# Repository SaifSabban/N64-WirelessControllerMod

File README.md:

# N64 -Wireless Controller Mod
A modification to your current N64 controller to make it wireless. Based on the Work by micro on the [Universal Wireless Retro Controller](https://nfggames.com/forum2/index.php?topic=5180.0) Click the photo to see a video of the controller in action.

<p align="center">

<p>

[!Youtube Tutorial Link (.../Extra/Images/Face.png)](http://www.youtube.com/shorts/WrgqsBNa95k)

<p align="center">
<iframe width="560 hight="315" src="http://www.youtube.com/shorts/WrgqsBNa95k" title="Youtube Tutorial Link" frameboarder="0"allow="accelerometer; autoplay; clipboard-write; encrypted-media; gyroscope; picture-in-picture" allowfullscreen></iframe>
</p>

href="http://www.youtube.com/shorts/WrgqsBNa95k" target="_blank"></a>
<p>

### Notes
This project could use a lot of work, mainly:
1. We could integrate the NRF24L01+ into the PCB boards.
2. Add the components of the Micro-LiPo into the main transmitter PCB Board.
3. Translate the assembly code into Arduino code to allow the use of smaller micro controllers and possibly 2-way communication.

If you press the A button while powering the N64 controller with the mod, you will set the channel to A, while if you press B, you will set it to Channel B.

Know that if you decide to undertake this project, you are the one liable for any damages or risks that might occur.

## Getting Started
### Prerequisites
All the Components that are needed can be found in the bellow list:
<p align="center"><p>

Optionally you could use JST connectors, instead of soldering wires directly to the PCB. I used the PH series.<br/>
you need to have an [ISP Arduino Programmer](https://docs.arduino.cc/built-in-examples/arduino-isp/ArduinoISP), or use any ISP programmer such as the [USBasp-Programmer](https://hobbycomponents.com/usb-interface/841-usbasp-avr-programmer-adaptor).<br/>
Install and set up [avrdudess](https://avrdudess.software.informer.com/2.4/) There are tons of write-ups on how to do this.<br/>
Print the Receiver's [3D box and Lid](https://github.com/saifsabban/N64-WirelessControllerMod/tree/master/3D-PrintableCase), and use two 2.5M screws to hold it down.<br/>
Print the PCBs for the [Reciever with a SMD microcontroller](https://github.com/saifsabban/N64-WirelessControllerMod/blob/master/N64_Receiver/N64_Receiver_PCB/N64_RX_GerberV2.1.zip) or [Receiver with a DIP microcontroller](https://github.com/saifsabban/N64-WirelessControllerMod/blob/master/N64_Receiver/N64_Receiver_PCB/N64_RX_GerberV2.0.zip) & the [Transmitter](https://github.com/saifsabban/N64-WirelessControllerMod/blob/master/N64_Transmitter/N64_Transmitter_PCB/N64_Tx_V4.0_Gerber.zip)

## Making the Receiver
1. Populate the Receiver PCB with the appropriate parts (The essential resistors & capacitor can be either SMD or Through-Hole):<br/><p align="center"><p>
2. Connect the ISP pins for your desired programmer to the Receiver Board. Hopefully this reference image and the PCB silkscreen will be of some help.<br/><p align="center"><p>
3. Program the Board using AVRdudess with the same parameters shown, MAKE SURE THAT THE HIGH BYTE IS 0xDF & LOW BYTE IS 0xEE. If you don't then you might never be able to use that microcontroller again unless you change the crystal<br/><p align="center"><p>
4. Solder some wire to the switch and solder the other side to the PCB board's SW connector (It doesn't matter which pole of the switch connects to which pad).
5. Cut the N64 plug from the controller, making sure you have some length to route & solder to, I usually keep amount 20cm of cable and cut as necessary.
6. Check the fit of the plug to the printed box, some 3D printers make the opening too large or too small.
7. Glue the Connector to the BOX.
8. Solder the Red wire to the + pad on the connector labelled N64, the black wire to the pad labelled - and the white wire to the pad in the middle of both + & -.
9. Attach (or solder) the NRF24L01+ board onto the Receiver PCB.
10. Place and glue all the parts inside the 3D printed box (As shown) and screw on the Lid<br/><p align="center"><p>

## Making the Transmitters
1. Populate the Transmitter PCB with the appropriate parts:<br/><p align="center"><p>
2. Connect the ISP pins for your desired programmer to the Transmitter Board. Hopefully this reference image will be of some help (the pins are in the same location as the connector on the Transmitter PCB, the Ground pin is the one that is highlighted)<br/><p align="center"><p>
3. Program the Board using AVRdudess with the same parameters shown, MAKE SURE THAT THE HIGH BYTE IS 0xDF & LOW BYTE IS 0xDF. If you don't then you might never be able to use that microcontroller again unless you change the crystal<br/><p align="center"><p>
4. Disassemble the N64 Controller.
5. Desolder the original blue connector that connects to the cable. (I would strongly advise soldering a JST 4 pin PH female connector as shown in the photo below)<br/><p align="center"><p>
6. Check the Size of your switch as around 4.8mm, and proceed to drill a 5mm hole at the button half of the controller (See images), solder some wires to them and screw them onto the controller<br/><p align="center"><p><br/><p align="center"><p>
7. Solder some wires to the 5mm LED and hotglue it into the hole that the old controller wire used to come out of. (Keep a note which wire is positive and which is negative) <br/><p align="center"><p>
8. route the wires switch and LED wires to the "Right Hand" area of the controller.<br/><p align="center"><p>
9. Remove the 2 lower "Crosses" that brace the buttons, from the bottom half of the controller.<br/><p align="center"><p>
10. solder wires to the "Bat" pin and the "GND" pin on the Adafruit Micro lipo.
11. Place the Micro lipo at the Right-hand side of the controller, and cut a bit off the corresponding top and bottom half edges to allow the USB charger through.<br/><p align="center"><p><br/><p align="center"><p>
12. Desolder the Pins on the NRF24L01+ and solder wires to each pin, remembering which wire corresponds to which pin.<br/><p align="center"><p>
13. leave some length and solder the other side of the wires from step 11 to the Custom board.<br/><p align="center"><p>
14. Solder the LED and Switch wires to the Main PCB, making sure the polarity of the LED wires are correct (- pin is Ground, + pin is 3.3V).
15. Solder the wires from the Micro lipo, to the Custom board's Bat pins, making sure that the Bat pin solders to the pin marked with a +.
16. Solder the wires From the N64 controller board to the custom board, Pin order is VCC (Denoted by the + sign on top), signal wire, and ground. <br/><p align="center"><p>
17. Attach a battery to the micro lipo and test the mod. Remember if you press the A button while powering the N64 controller with the mod, you will set the channel to A, while if you press B, you will set it to Channel B.
18. If all works button up your device. I recommend routing the battery to the Left hand side of the controller, the custom board to the Right, and feeding the NRF24L01+ into the nook of the expantion slot.<br/><p align="center"><p>

## Warnings!!
Make sure the polarity of the receiver pins is correct or you risk blowing the N64's power module, or worse, frying the N64 completely. In you connect the Batter pins or the N64 pins to the wrong wires you risk frying you N64 controller. I've tried this mod on reproduction N64 controllers, but it seems they allow some electrical noise that messes us the communication pathways and making it seem like you've pressed buttons you didn't actually press. If you mess with the power pins on the NRF24L01+ you risk breaking either your n64 or the controller, depending on which one was wrongfully connected. However, messing up the data pins of the NRF24L01+ breaks nothing. If the battery is too low, it will keep the LED light on, but might not send any control signals to the receiver.

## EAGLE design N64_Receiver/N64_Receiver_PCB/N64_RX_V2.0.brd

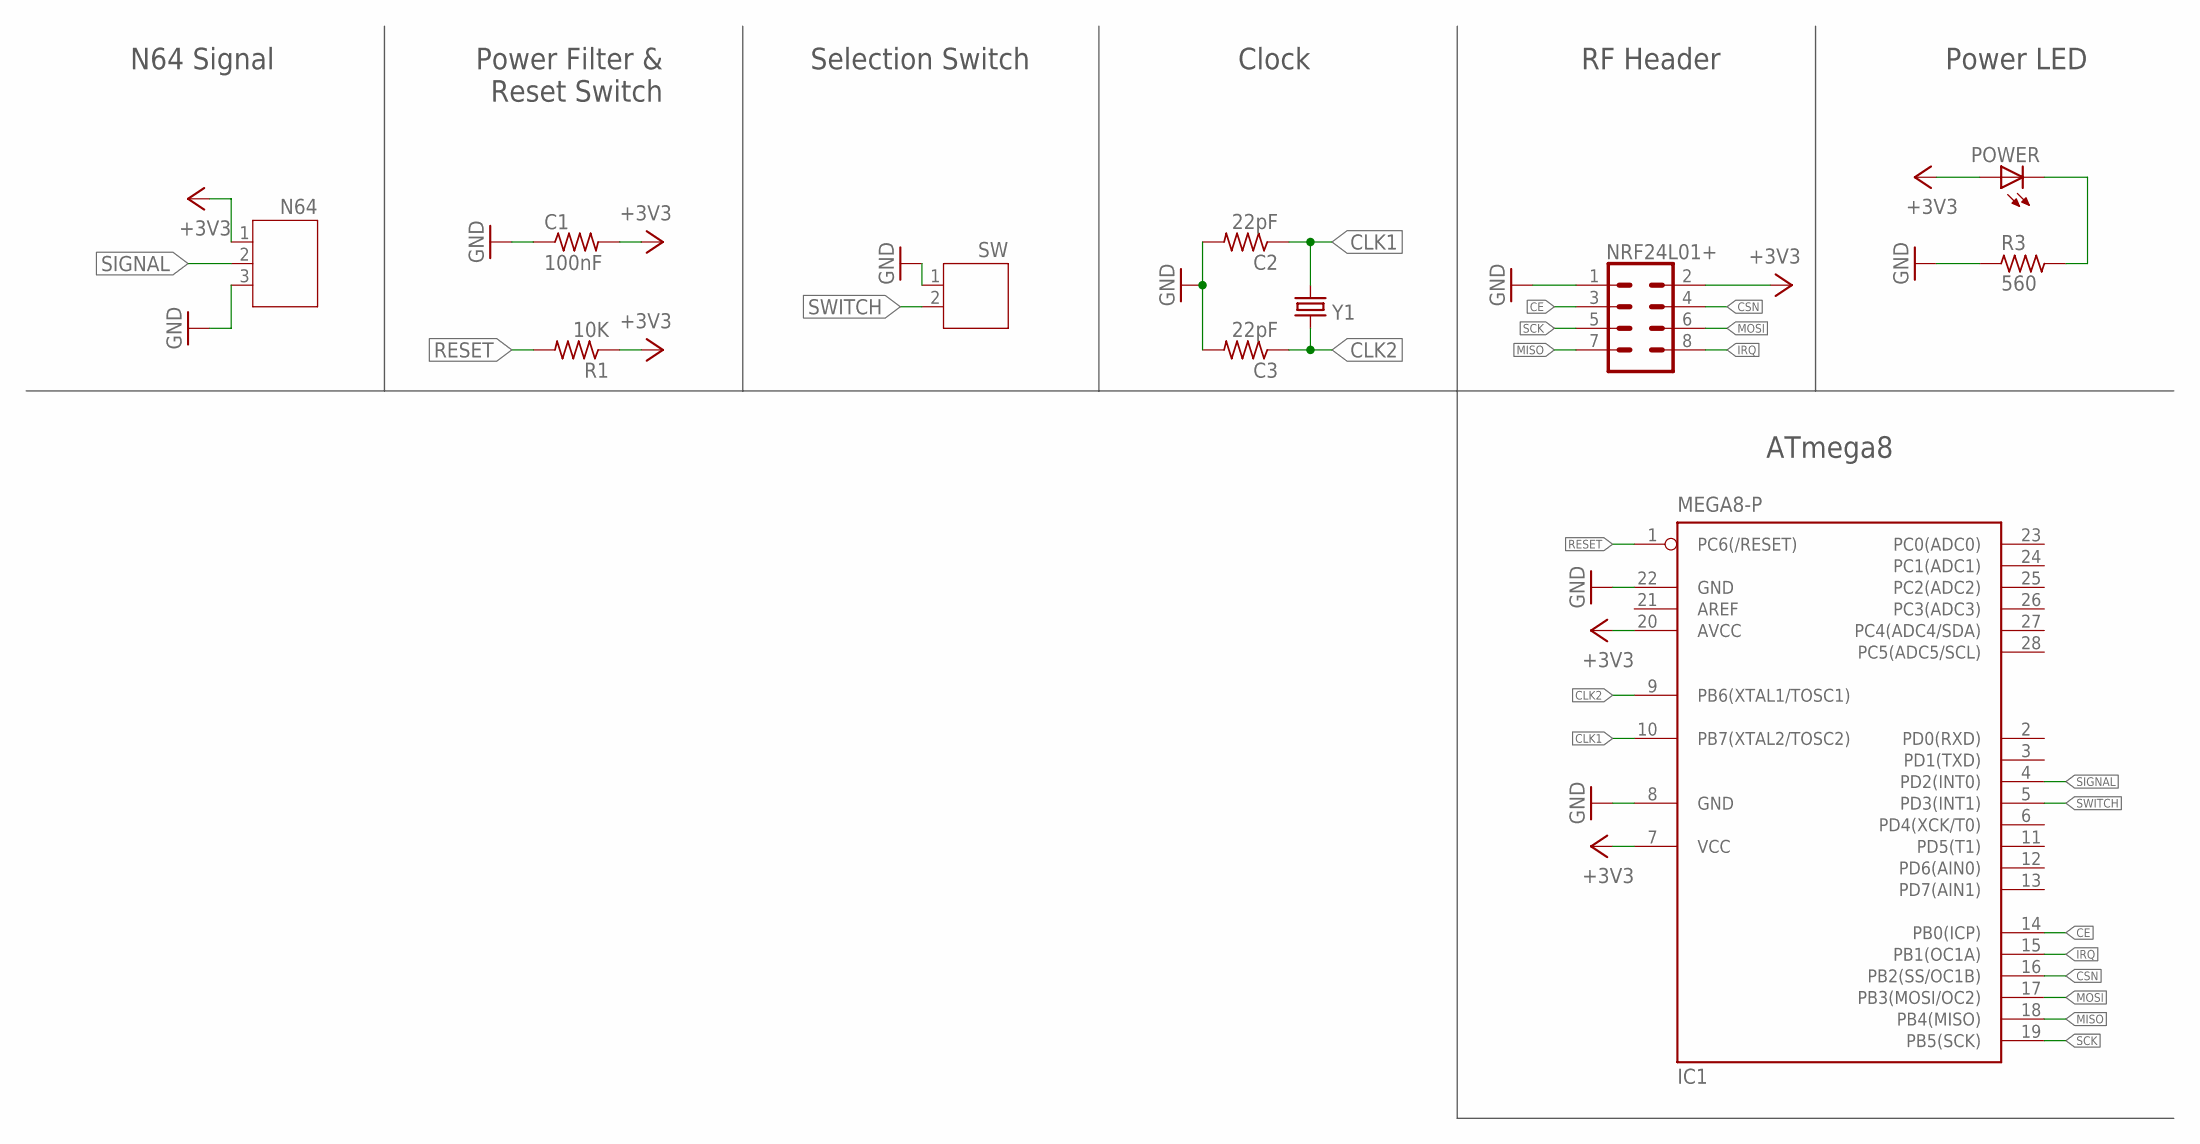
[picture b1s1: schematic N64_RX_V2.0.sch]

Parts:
C1: 100nF; 0805-THM
C2, C3: 22pF; 0805-THM
IC1: MEGA8-P; DIL28-3
N64: JST-PH3TH; JST-PH3
NRF24L01+: CONN_04X2; 2X4
POWER: LEDCHIPLED_0805; CHIPLED_0805
R1: 10K; 0805-THM
R3: 560; R0805
SW: JST-PH2TH; JST-PH2
Y1: CRYSTALHC49S; HC49/S

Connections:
+3V3: C1.2, IC1.7 (VCC), IC1.20 (AVCC), N64.1, NRF24L01+.2, POWER.A, R1.1
CE: IC1.14 (PB0(ICP)), NRF24L01+.3
CLK1: C2.1, IC1.10 (PB7(XTAL2/TOSC2)), Y1.2
CLK2: C3.1, IC1.9 (PB6(XTAL1/TOSC1)), Y1.1
CSN: IC1.16 (PB2(SS/OC1B)), NRF24L01+.4
GND: C1.1, C2.2, C3.2, IC1.8 (GND), IC1.22 (GND), N64.3, NRF24L01+.1, R3.1, SW.1
IRQ: IC1.15 (PB1(OC1A)), NRF24L01+.8
MISO: IC1.18 (PB4(MISO)), NRF24L01+.7
MOSI: IC1.17 (PB3(MOSI/OC2)), NRF24L01+.6
unnamed: POWER.C, R3.2
RESET: IC1.1 (PC6(/RESET)), R1.2
SCK: IC1.19 (PB5(SCK)), NRF24L01+.5
SIGNAL: IC1.4 (PD2(INT0)), N64.2
SWITCH: IC1.5 (PD3(INT1)), SW.2

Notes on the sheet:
N64 Signal
Power Filter & Reset Switch
Selection Switch
Clock
RF Header
ATmega8
Power LED

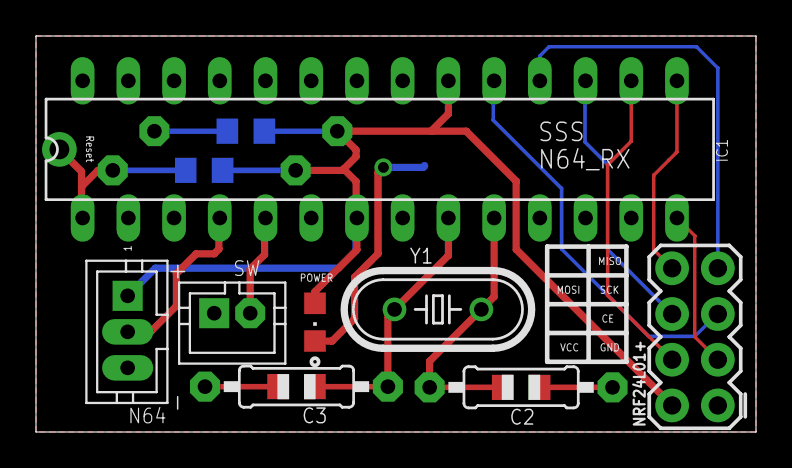
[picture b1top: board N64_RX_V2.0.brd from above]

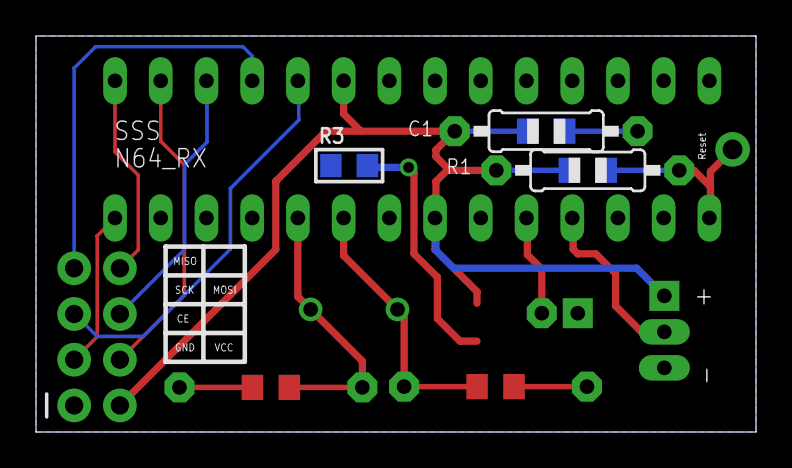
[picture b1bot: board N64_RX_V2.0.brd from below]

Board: 2 copper layers, 40.0 x 22.0 mm, 11 parts (3 on the bottom side), 14 nets.

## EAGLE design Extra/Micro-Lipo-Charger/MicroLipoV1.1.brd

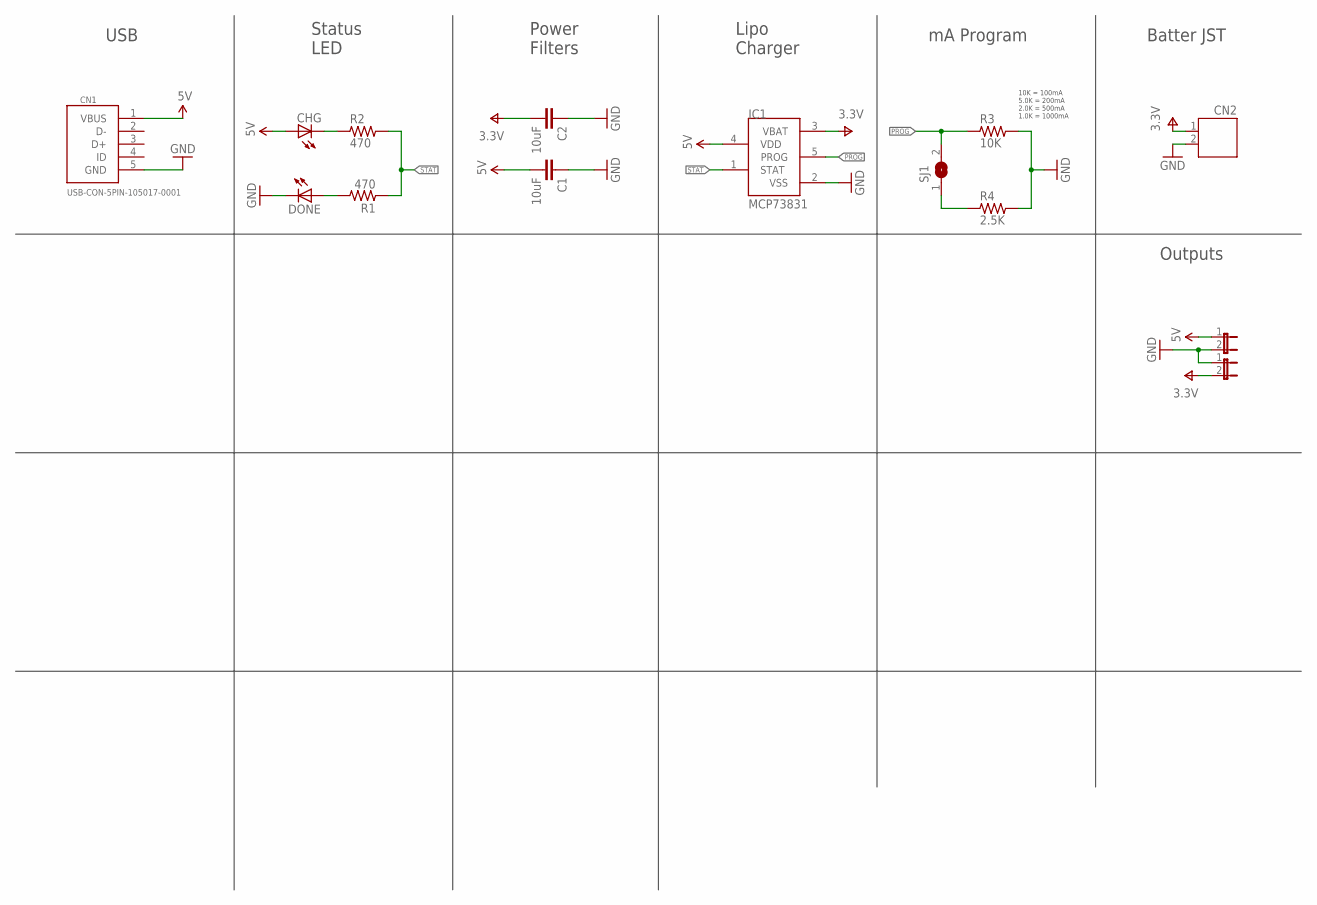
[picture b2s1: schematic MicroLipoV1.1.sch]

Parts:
C1, C2: 10uF; C0805K
CHG: LEDCHIPLED_0805; CHIPLED_0805
CN1: USB-CON-5PIN-105017-0001; USB-MICRO-MOLEX-105017-0001
CN2: JST-PH2; JST-PH2-S2B
DONE: LEDCHIPLED_0805; CHIPLED_0805
IC1: MCP73831; SOT23-5L
JP2, JP3: JUMPER-2PTH; 1X02
R1, R2: 470; R0805
R3: 10K; R0805
R4: 2.5K; R0805
SJ1: SJ

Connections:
5V: C1.2, CHG.A, CN1.1 (VBUS), IC1.4 (VDD), JP2.1
GND: C1.1, C2.1, CN1.5 (GND), CN2.2, DONE.C, IC1.2 (VSS), JP2.2, JP3.1, R3.2, R4.2
unnamed: CHG.C, R2.1
unnamed: DONE.A, R1.2
unnamed: R4.1, SJ1.1
PROG: IC1.5 (PROG), R3.1, SJ1.2
STAT: IC1.1 (STAT), R1.1, R2.2
V+: C2.2, CN2.1, IC1.3 (VBAT), JP3.2

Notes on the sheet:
USB
Status LED
Power Filters
Lipo Charger
mA Program
Batter JST
Outputs
10K = 100mA 5.0K = 200mA 2.0K = 500mA 1.0K = 1000mA

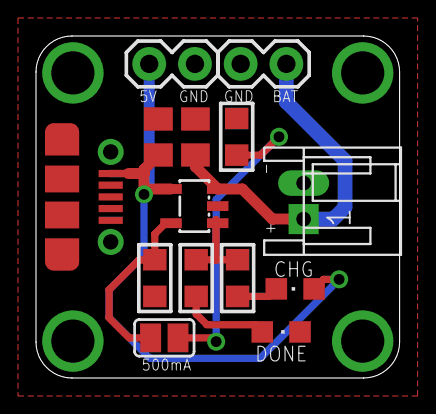
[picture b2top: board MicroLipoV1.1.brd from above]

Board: 2 copper layers, 20.2 x 19.0 mm, 14 parts (0 on the bottom side), 8 nets.

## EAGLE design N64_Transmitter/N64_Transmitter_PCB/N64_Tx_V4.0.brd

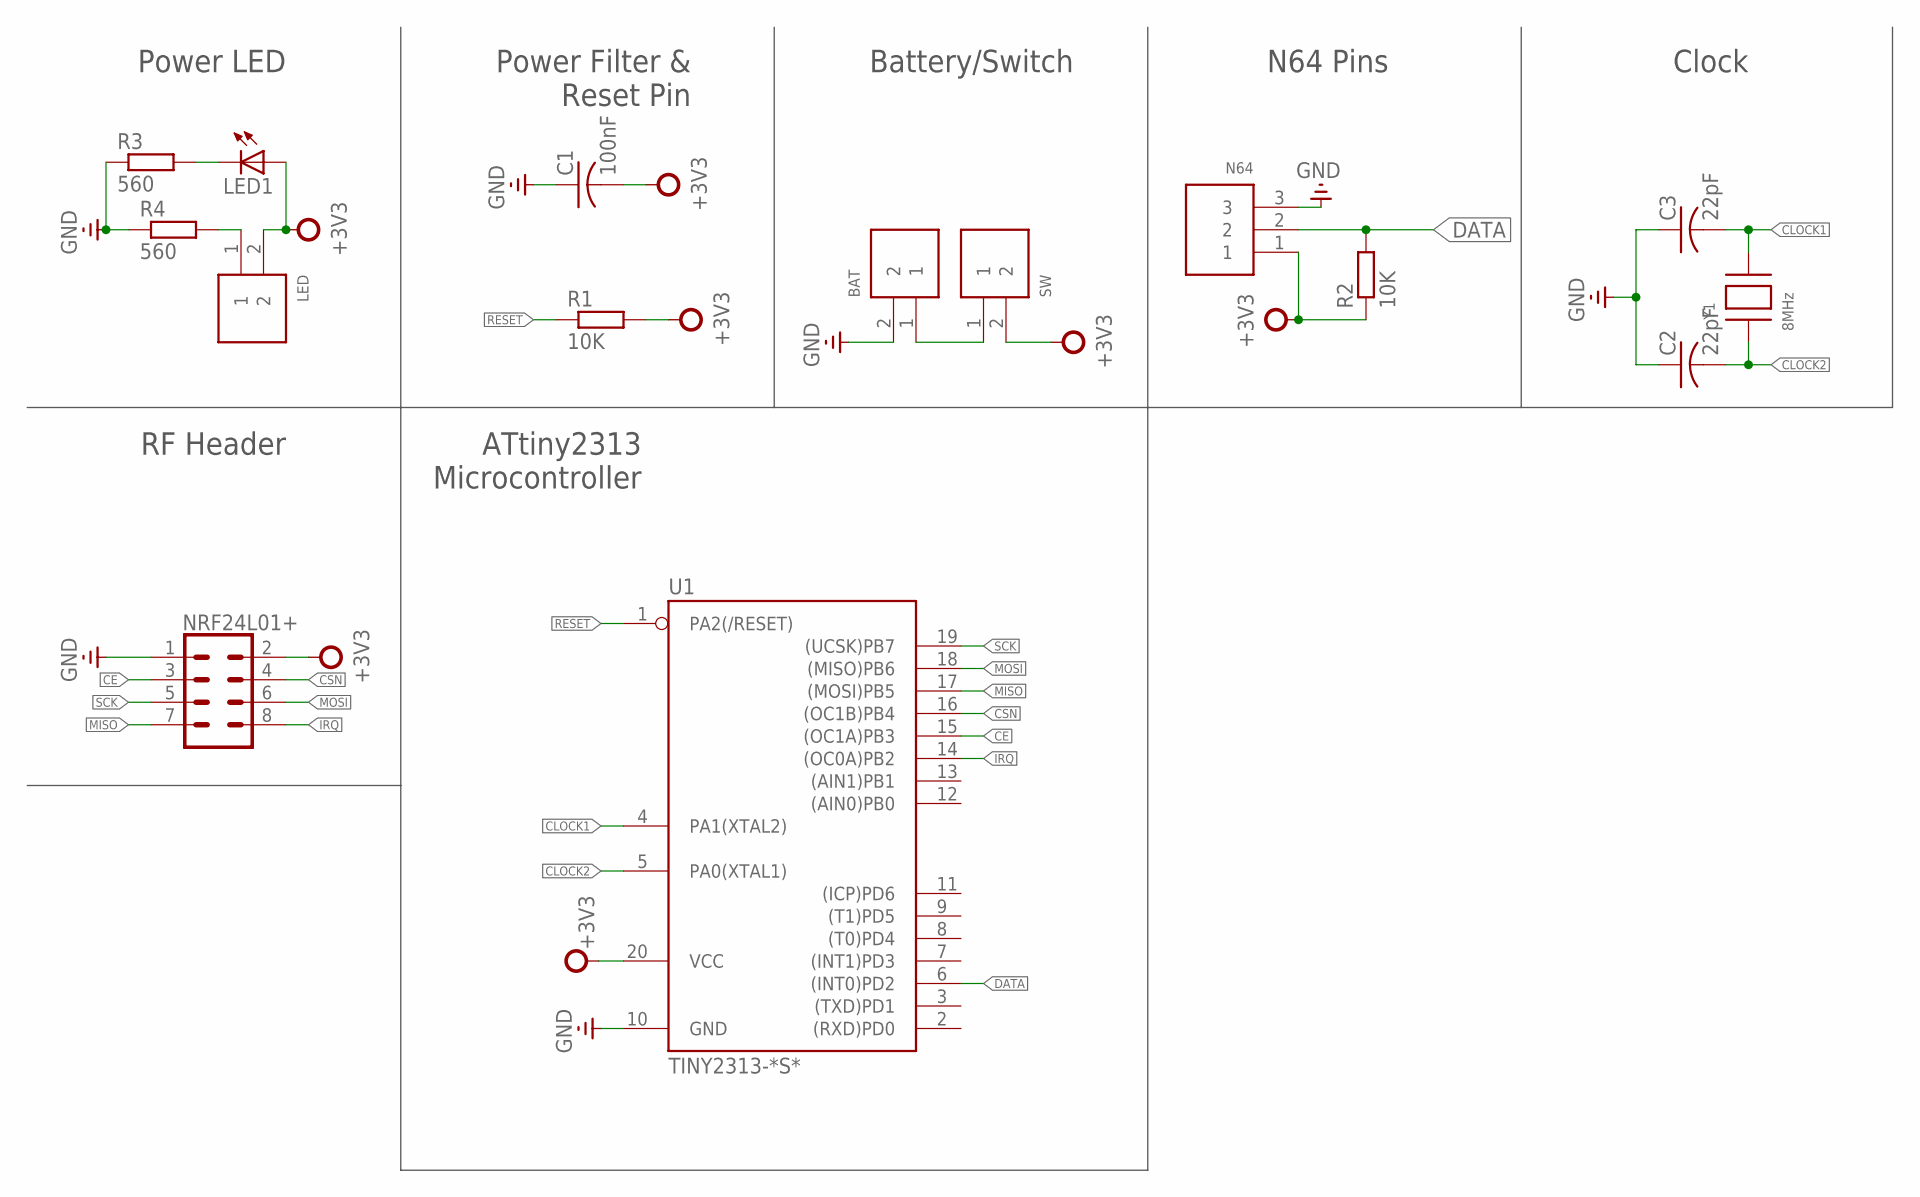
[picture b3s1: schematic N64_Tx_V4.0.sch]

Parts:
BAT: 2PIN; B2B-PH-K-S
C1: 100nF; C0603
C2, C3: 22pF; C0603
LED: 2PIN; B2B-PH-K-S
LED1: LEDCHIPLED_0805; CHIPLED_0805
N64: 3PIN; B3B-PH-K-S
NRF24L01+: CONN_04X2; 2X4
R1, R2: 10K; R0603
R3, R4: 560; R0603
SW: 2PIN; B2B-PH-K-S
U1: TINY2313-*S*; SO20L$
Y1: 8MHz; QANTEK_SMD_CRYSTAL_PACK

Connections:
+3V3: C1.2, LED.2, LED1.A, N64.1, NRF24L01+.2, R1.2, R2.1, SW.2, U1.20 (VCC)
CE: NRF24L01+.3, U1.15 ((OC1A)PB3)
CLOCK1: C3.2, U1.4 (PA1(XTAL2)), Y1.P$2 (X2)
CLOCK2: C2.2, U1.5 (PA0(XTAL1)), Y1.P$1 (X1)
CSN: NRF24L01+.4, U1.16 ((OC1B)PB4)
DATA: N64.2, R2.2, U1.6 ((INT0)PD2)
GND: BAT.2, C1.1, C2.1, C3.1, N64.3, NRF24L01+.1, R3.1, R4.1, U1.10 (GND)
IRQ: NRF24L01+.8, U1.14 ((OC0A)PB2)
MISO: NRF24L01+.7, U1.17 ((MOSI)PB5)
MOSI: NRF24L01+.6, U1.18 ((MISO)PB6)
unnamed: BAT.1, SW.1
unnamed: LED1.C, R3.2
unnamed: LED.1, R4.2
RESET: R1.1, U1.1 (PA2(/RESET))
SCK: NRF24L01+.5, U1.19 ((UCSK)PB7)

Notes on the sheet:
Power LED
Power Filter & Reset Pin
Battery/Switch
N64 Pins
Clock
RF Header
ATtiny2313 Microcontroller

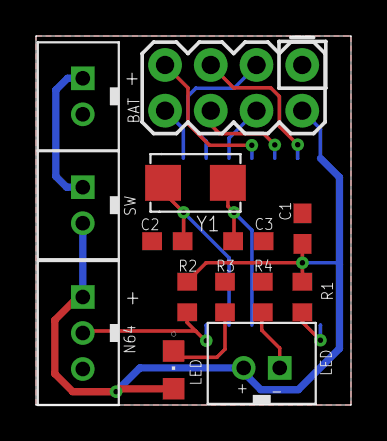
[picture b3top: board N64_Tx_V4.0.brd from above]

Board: 2 copper layers, 17.5 x 20.5 mm, 15 parts (1 on the bottom side), 15 nets.

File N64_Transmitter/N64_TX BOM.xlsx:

Part | Value | Footprint | RS Code
C1 | 100 nF | 0402 | 425-1510 |  | or a 0805 | 378-542
C2 | 22pF | 0805 | 264-4258
C3 | 22pF | 0805 | 264-4258
IC1 | ATtiny2313 |  | 133-0978
LED1 | 2mA
LED2 | Normal LED | 0805
Y1 | 8MHz Crystal | Special | 187-5995
R1 | 10k Ohm | 0805 | 432-450 |  | or a 0402 | 430-767
R2 | 10k Ohm | 0805 | 432-450 |  | or a 0402 | 430-767
R3 | 560 Ohm | 0402 | 667-8668 |  | or a 0805 | 432-450
S1 | Switch |  | 734-7154
NRF24L01+ | RF | 2x4 SIL | ebay.co.uk/i/293157600466?chn=ps&var=592026070810&norover=1&mkevt=1&mkrid=710-1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
Diode?

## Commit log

2020-06-21 Create file
2020-06-21 Create Micro-Lipo-Charger
2022-05-18 Adding all the files
2022-05-18 Readme Formation
2022-05-18 Readme Transmitter
2022-05-18 Readme Reciever
2022-05-18 Readme Reciever fix
2022-05-18 Readme fix
2022-05-18 Fixing Youtube Face
2022-05-18 Added Dip Controller
2022-05-18 Added Extra Photos
2022-05-18 Fixing up readme
2022-05-23 Finishing up Readme

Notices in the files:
parts and their libraries:
GeekAmmo: Licensing:Creative Commons ShareAlike 4.0 International - https://creativecommons.org/licenses/by-sa/4.0
rc-master-smd: Copyright (C) 2007, Bob Starr
SparkFun: Licensing: CC v3.0 Share-Alike You are welcome to use this library for commercial purposes.
